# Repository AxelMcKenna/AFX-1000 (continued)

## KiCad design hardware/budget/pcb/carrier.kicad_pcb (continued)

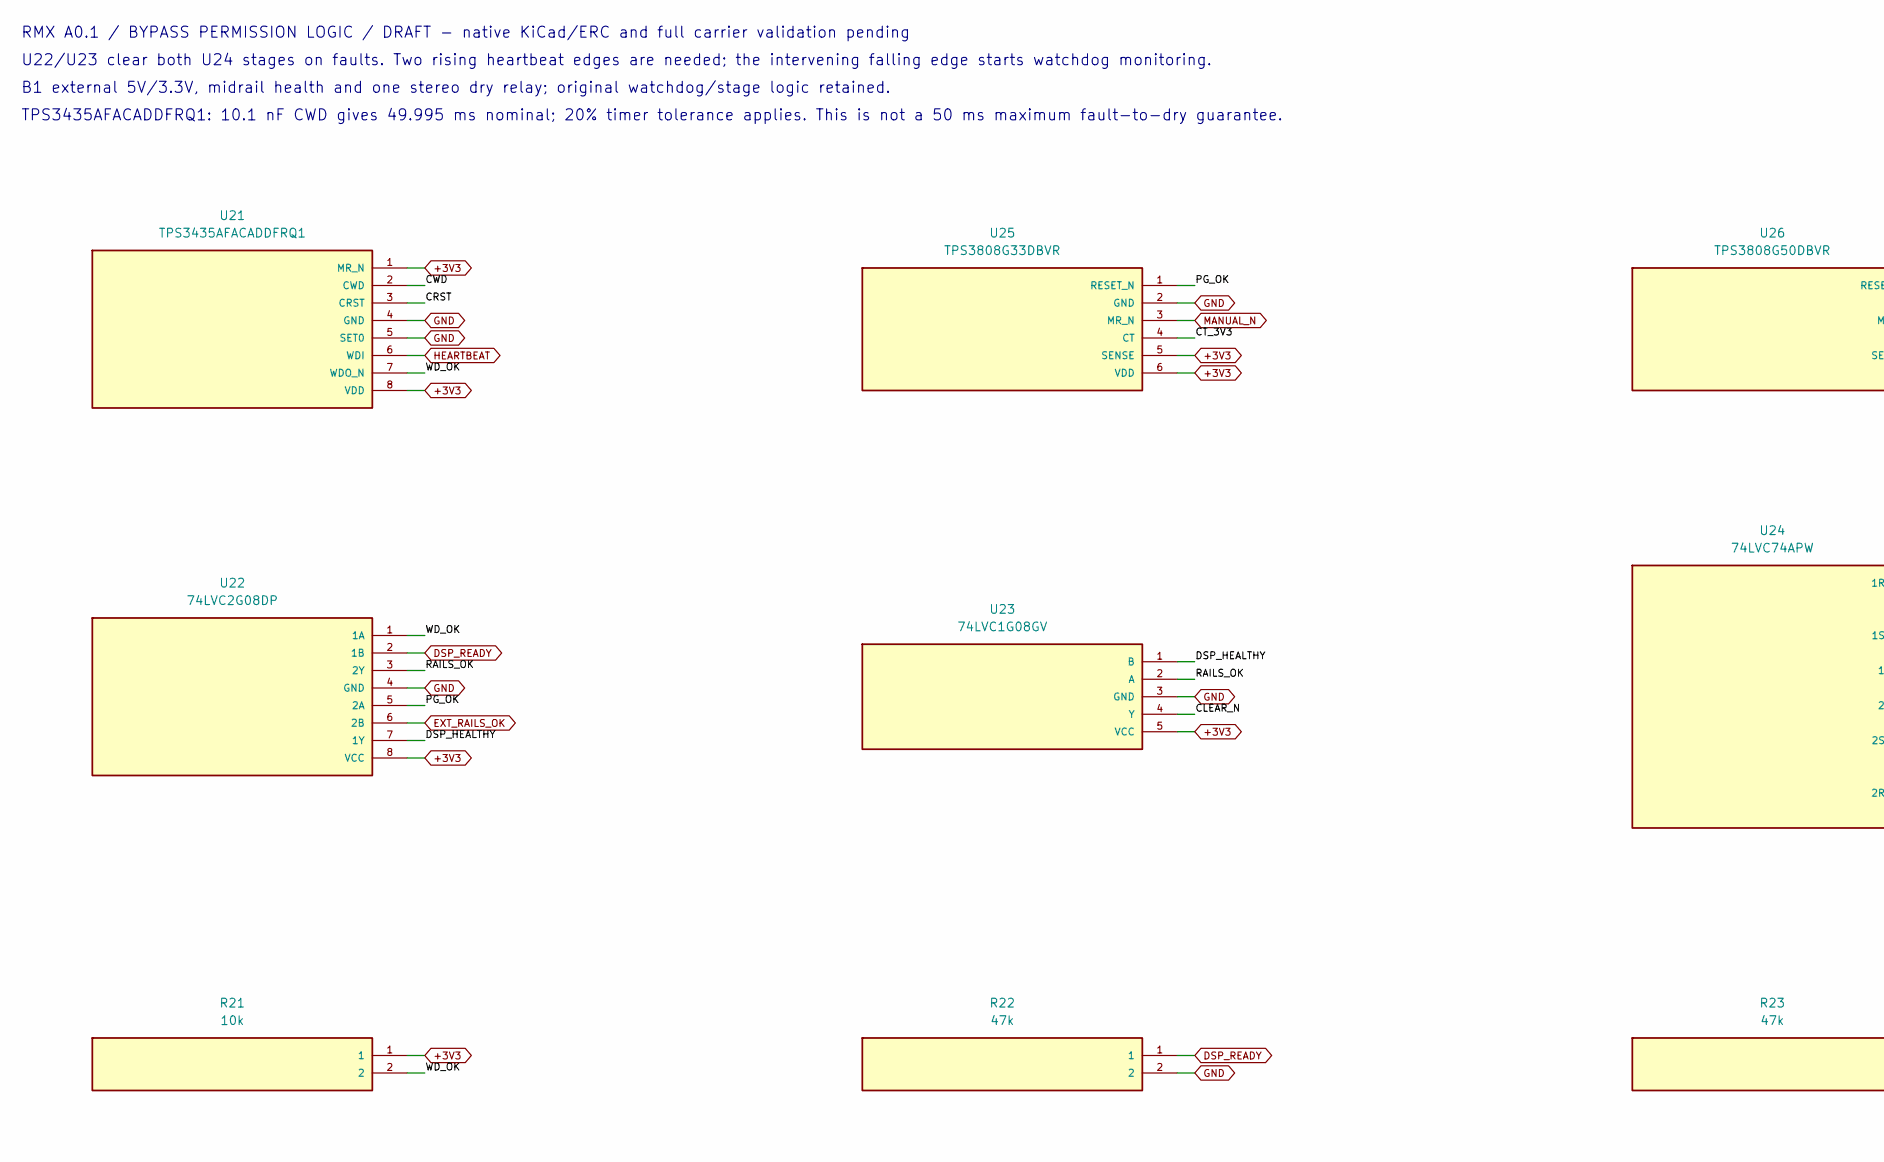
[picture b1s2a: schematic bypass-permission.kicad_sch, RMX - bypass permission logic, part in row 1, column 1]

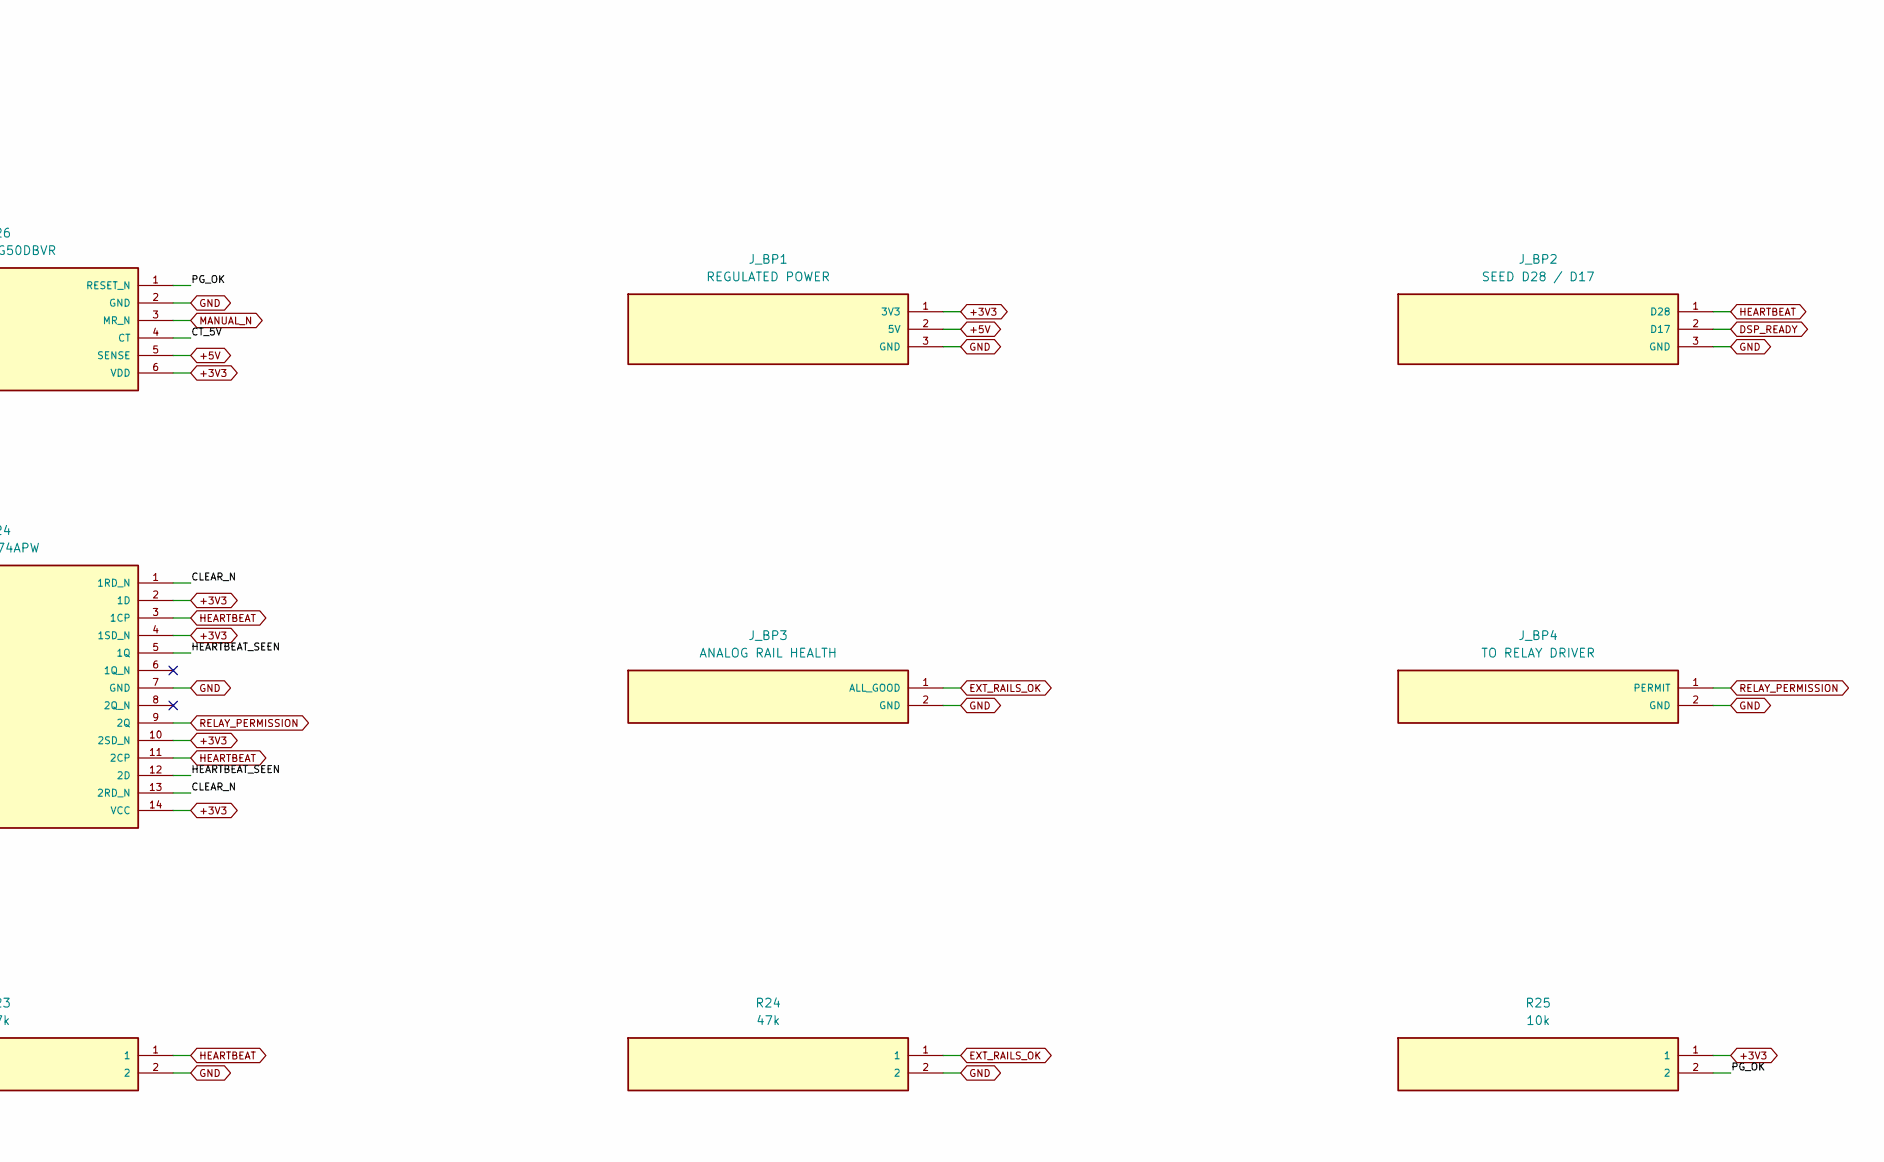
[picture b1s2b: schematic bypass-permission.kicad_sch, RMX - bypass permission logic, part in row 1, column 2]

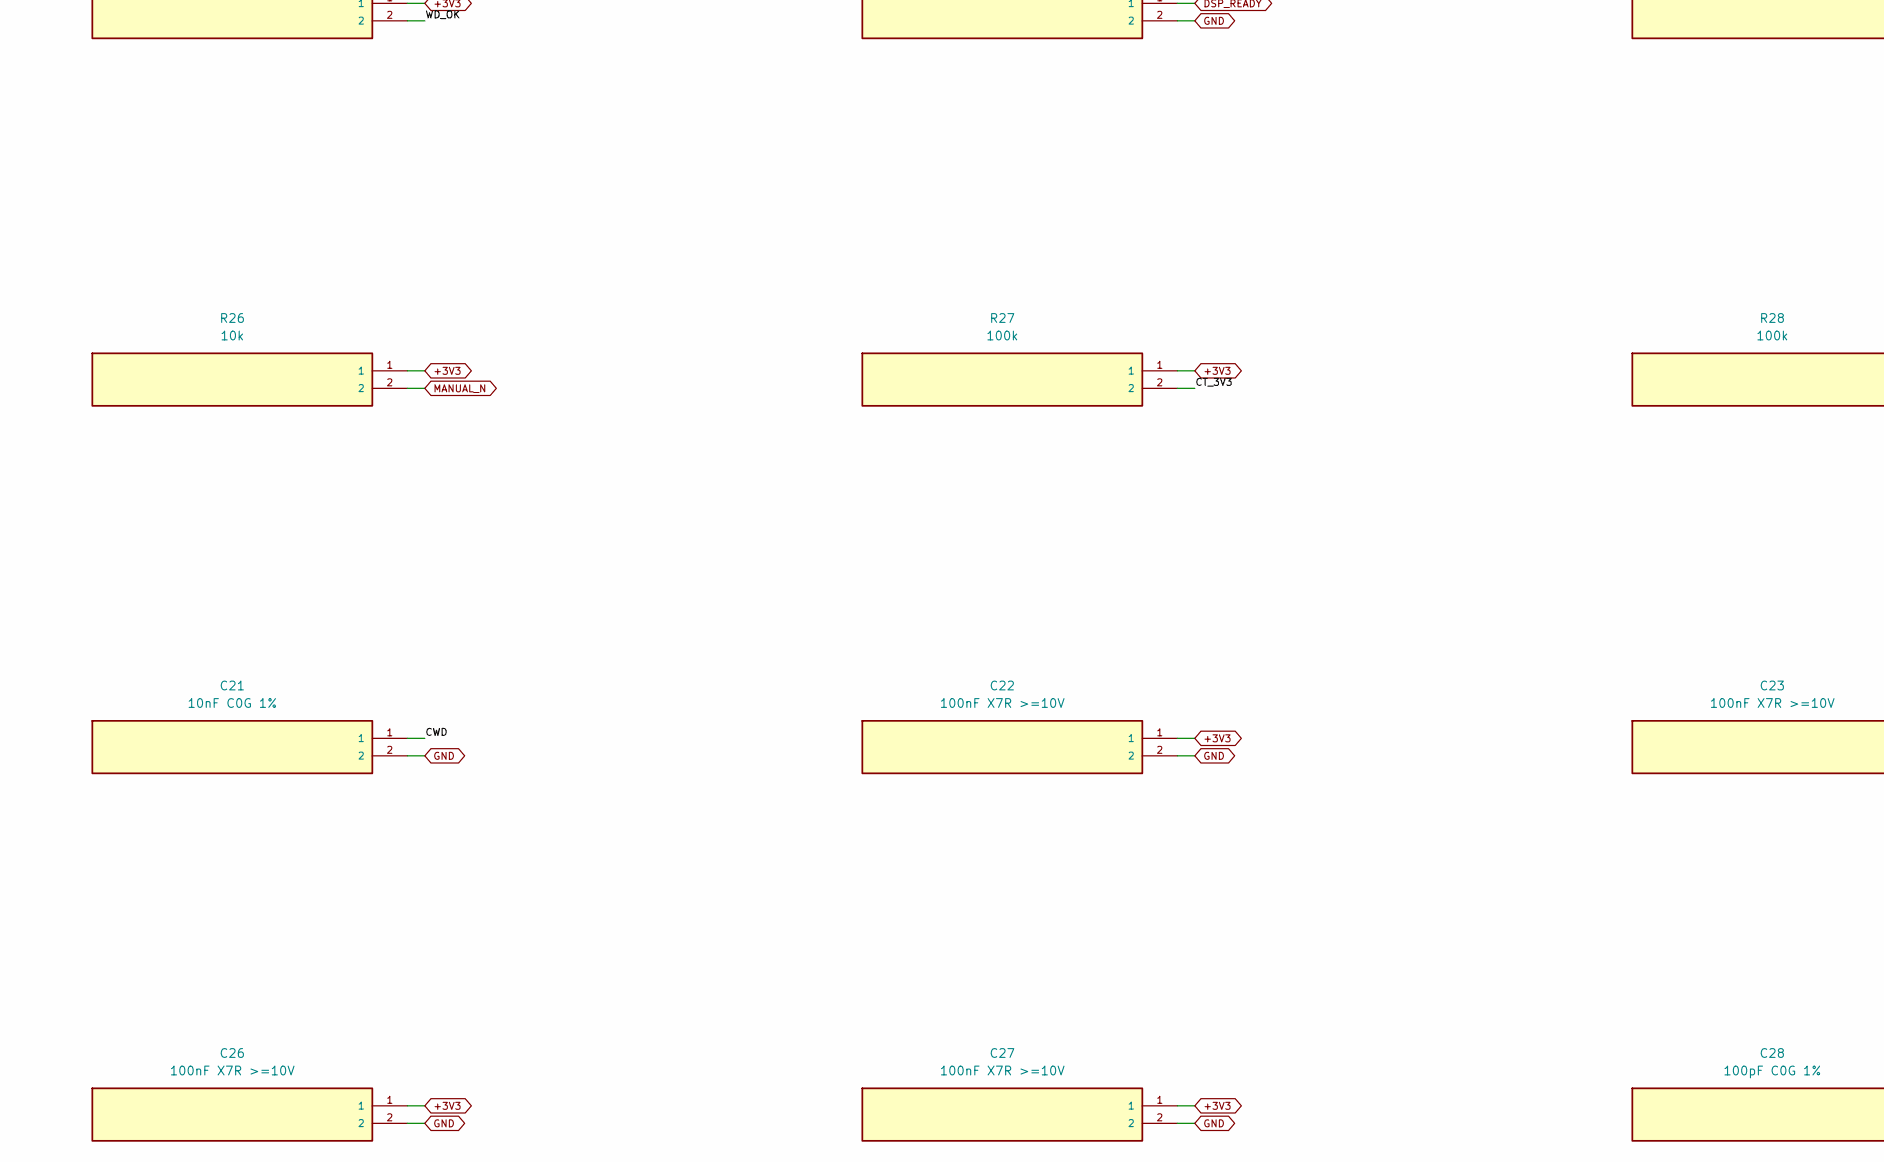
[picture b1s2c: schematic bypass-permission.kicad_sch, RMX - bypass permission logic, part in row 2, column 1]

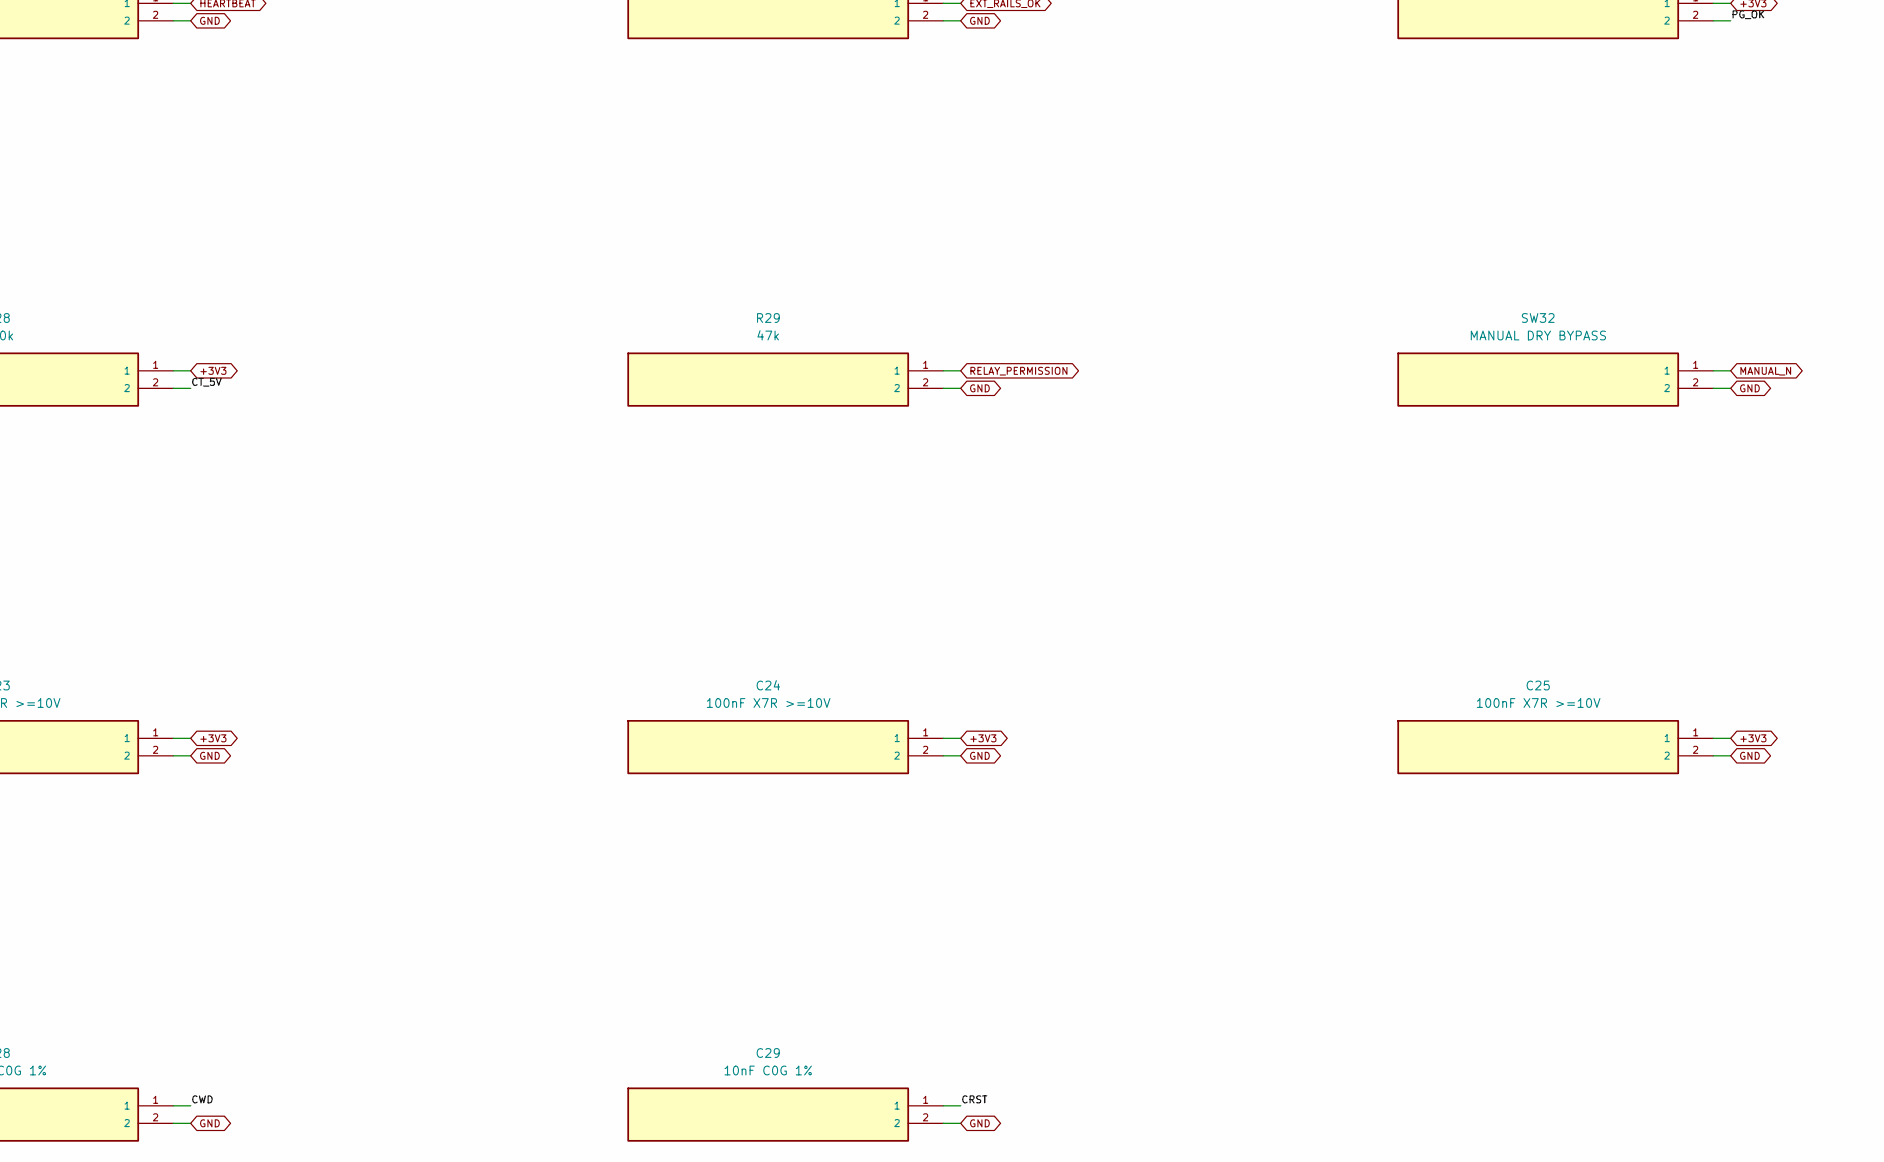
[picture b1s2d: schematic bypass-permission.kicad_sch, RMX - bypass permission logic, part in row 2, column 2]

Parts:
C21, C29: 10nF C0G 1%; C_0805_2012Metric; MPN C0805X103F5GACTU
C22, C23, C24, C25, C26, C27: 100nF X7R >=10V; C_0603_1608Metric
C28: 100pF C0G 1%; C_0603_1608Metric; MPN C0603C101F5GACTU
J_BP1: REGULATED POWER; PinHeader_1x03_P2.54mm_Vertical
J_BP2: SEED D28 / D17; PinHeader_1x03_P2.54mm_Vertical
J_BP3: ANALOG RAIL HEALTH; PinHeader_1x02_P2.54mm_Vertical
J_BP4: TO RELAY DRIVER; PinHeader_1x02_P2.54mm_Vertical
R21, R25, R26: 10k; R_0603_1608Metric; MPN RC0603FR-0710KL
R22, R23, R24, R29: 47k; R_0603_1608Metric; MPN RC0603FR-0747KL
R27, R28: 100k; R_0603_1608Metric; MPN RC0603FR-07100KL
SW32: MANUAL DRY BYPASS
U21: TPS3435AFACADDFRQ1; Texas_DDF0008A_SOT-8_1.6x2.9mm_P0.65mm; MPN TPS3435AFACADDFRQ1
U22: 74LVC2G08DP; TSSOP-8_3x3mm_P0.65mm; MPN 74LVC2G08DP
U23: 74LVC1G08GV; SOT-23-5; MPN 74LVC1G08GV
U24: 74LVC74APW; TSSOP-14_4.4x5mm_P0.65mm; MPN 74LVC74APW,118
U25: TPS3808G33DBVR; SOT-23-6; MPN TPS3808G33DBVR
U26: TPS3808G50DBVR; SOT-23-6; MPN TPS3808G50DBVR

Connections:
+3V3: C22.1, C23.1, C24.1, C25.1, C26.1, C27.1, J_BP1.1 (3V3), R21.1, R25.1, R26.1, R27.1, R28.1, U21.1 (MR_N), U21.8 (VDD), U22.8 (VCC), U23.5 (VCC), U24.2 (1D), U24.4 (1SD_N), U24.10 (2SD_N), U24.14 (VCC), U25.5 (SENSE), U25.6 (VDD), U26.6 (VDD); also elsewhere on the board
+5V: J_BP1.2 (5V), U26.5 (SENSE); also elsewhere on the board
/bypass-permission/CLEAR_N: U23.4 (Y), U24.1 (1RD_N), U24.13 (2RD_N)
/bypass-permission/CRST: C29.1, U21.3 (CRST)
/bypass-permission/CT_3V3: R27.2, U25.4 (CT)
/bypass-permission/CT_5V: R28.2, U26.4 (CT)
/bypass-permission/CWD: C21.1, C28.1, U21.2 (CWD)
/bypass-permission/DSP_HEALTHY: U22.7 (1Y), U23.1 (B)
/bypass-permission/HEARTBEAT_SEEN: U24.5 (1Q), U24.12 (2D)
/bypass-permission/PG_OK: R25.2, U22.5 (2A), U25.1 (RESET_N), U26.1 (RESET_N)
/bypass-permission/RAILS_OK: U22.3 (2Y), U23.2 (A)
/bypass-permission/WD_OK: R21.2, U21.7 (WDO_N), U22.1 (1A)
DSP_READY: J_BP2.2 (D17), R22.1, U22.2 (1B)
EXT_RAILS_OK: J_BP3.1 (ALL_GOOD), R24.1, U22.6 (2B); also elsewhere on the board
GND: C21.2, C22.2, C23.2, C24.2, C25.2, C26.2, C27.2, C28.2, C29.2, J_BP1.3 (GND), J_BP2.3 (GND), J_BP3.2 (GND), J_BP4.2 (GND), R22.2, R23.2, R24.2, R29.2, SW32.2, U21.4 (GND), U21.5 (SET0), U22.4 (GND), U23.3 (GND), U24.7 (GND), U25.2 (GND), U26.2 (GND); also elsewhere on the board
HEARTBEAT: J_BP2.1 (D28), R23.1, U21.6 (WDI), U24.3 (1CP), U24.11 (2CP)
MANUAL_N: R26.2, SW32.1, U25.3 (MR_N), U26.3 (MR_N); also elsewhere on the board
RELAY_PERMISSION: J_BP4.1 (PERMIT), R29.1, U24.9 (2Q); also elsewhere on the board

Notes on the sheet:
RMX A0.1 / BYPASS PERMISSION LOGIC / DRAFT - native KiCad/ERC and full carrier validation pending
U22/U23 clear both U24 stages on faults. Two rising heartbeat edges are needed; the intervening falling edge starts watchdog monitoring.
B1 external 5V/3.3V, midrail health and one stereo dry relay; original watchdog/stage logic retained.
TPS3435AFACADDFRQ1: 10.1 nF CWD gives 49.995 ms nominal; 20% timer tolerance applies. This is not a 50 ms maximum fault-to-dry guarantee.

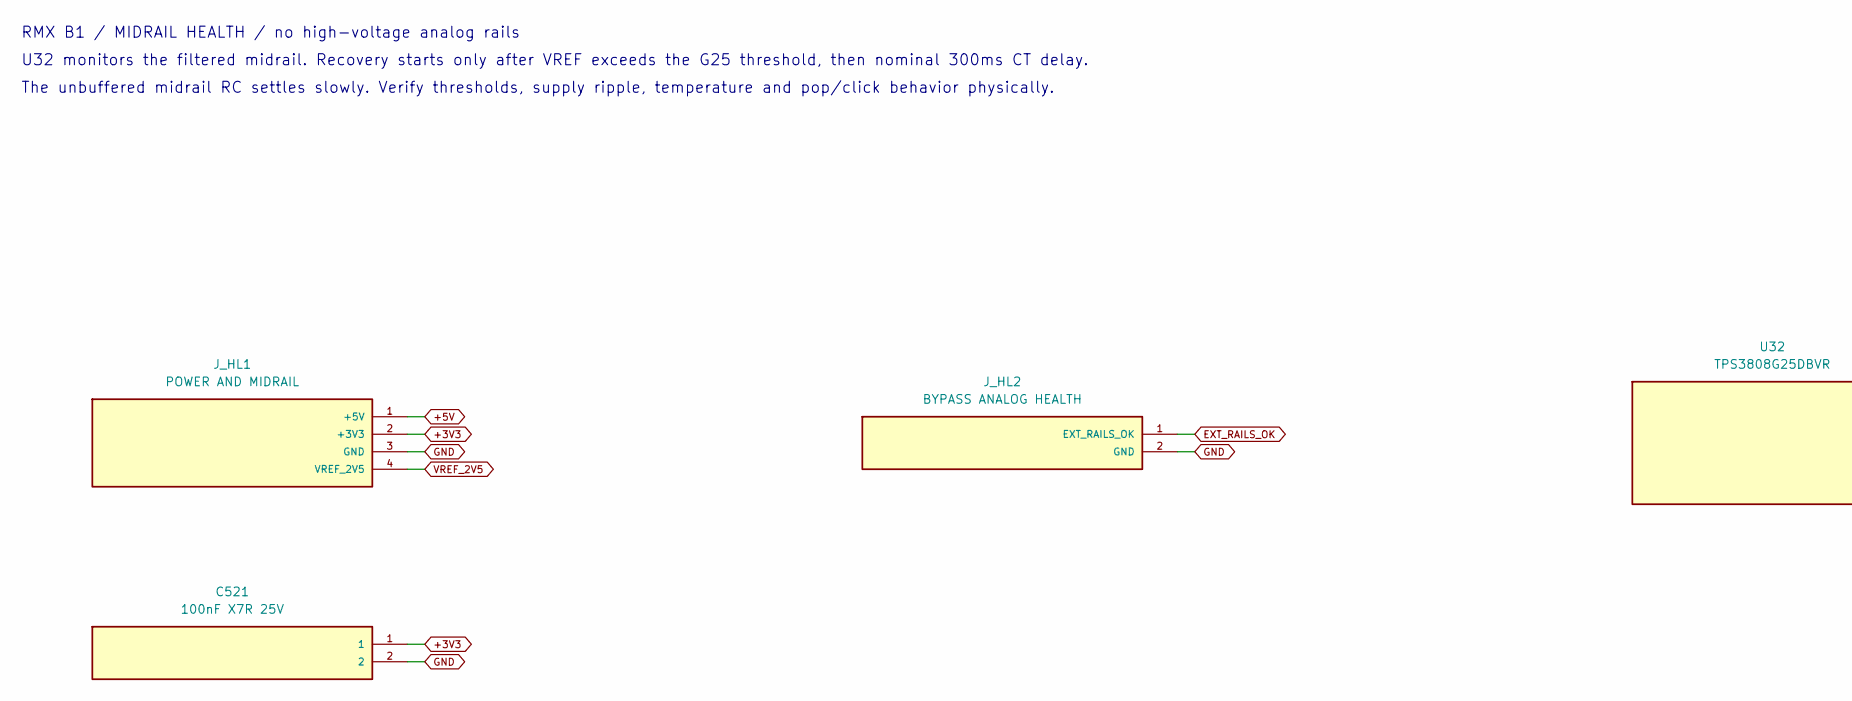
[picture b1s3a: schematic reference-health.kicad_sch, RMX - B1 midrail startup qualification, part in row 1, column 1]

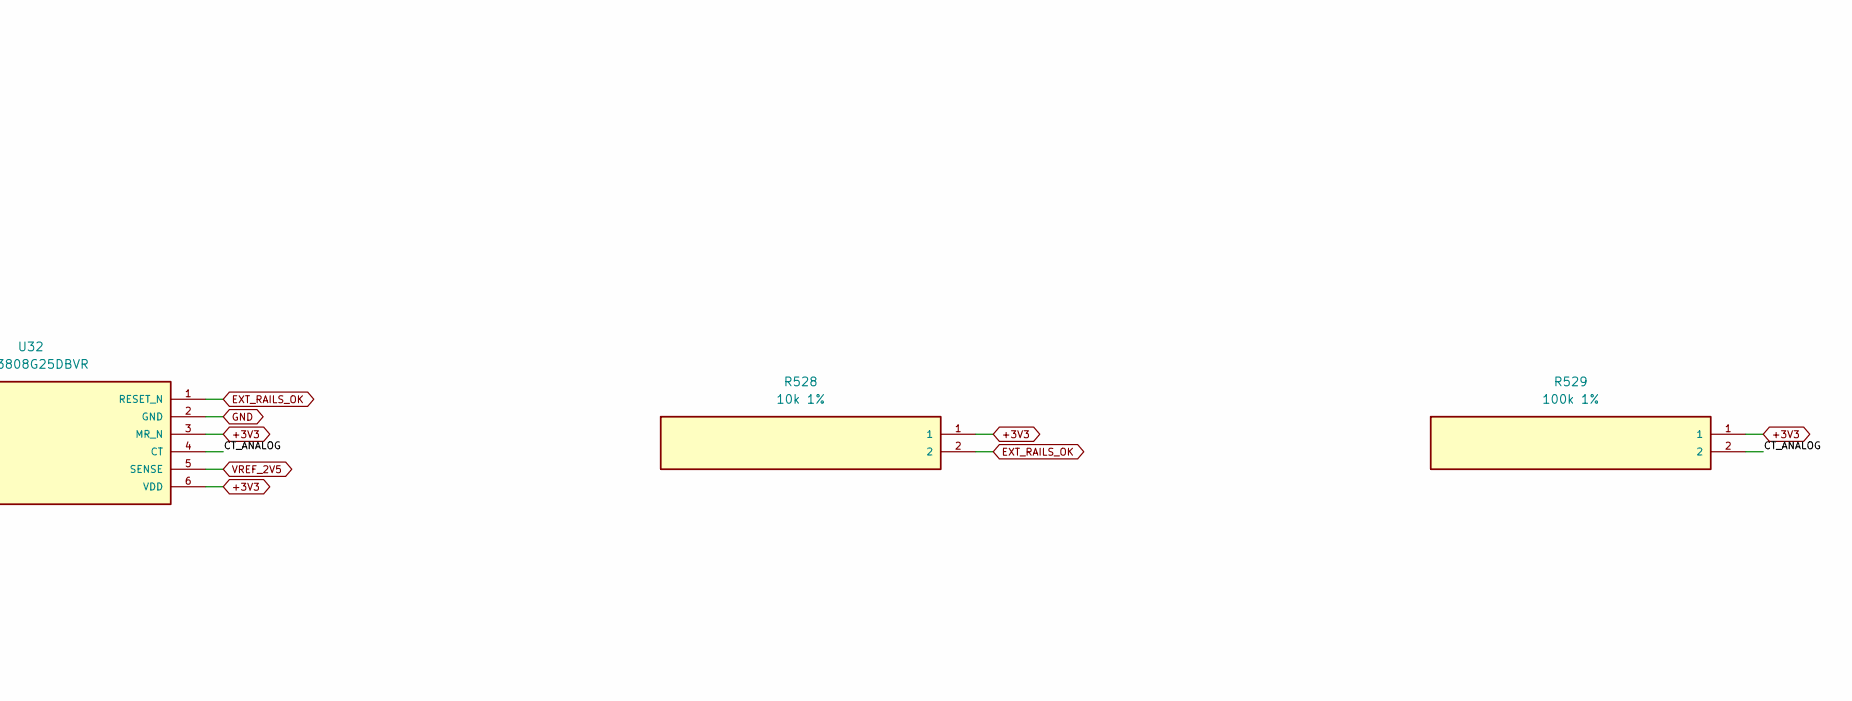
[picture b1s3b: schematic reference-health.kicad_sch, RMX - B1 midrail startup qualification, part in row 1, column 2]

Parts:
C521: 100nF X7R 25V; C_0805_2012Metric
J_HL1: POWER AND MIDRAIL; PinHeader_1x04_P2.54mm_Vertical
J_HL2: BYPASS ANALOG HEALTH; PinHeader_1x02_P2.54mm_Vertical
R528: 10k 1%; R_0603_1608Metric; MPN RC0603FR-0710KL
R529: 100k 1%; R_0603_1608Metric; MPN RC0603FR-07100KL
U32: TPS3808G25DBVR; SOT-23-6; MPN TPS3808G25DBVR

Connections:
+3V3: C521.1, J_HL1.2 (+3V3), R528.1, R529.1, U32.3 (MR_N), U32.6 (VDD); also elsewhere on the board
+5V: J_HL1.1 (+5V); also elsewhere on the board
/reference-health/CT_ANALOG: R529.2, U32.4 (CT)
EXT_RAILS_OK: J_HL2.1 (EXT_RAILS_OK), R528.2, U32.1 (RESET_N); also elsewhere on the board
GND: C521.2, J_HL1.3 (GND), J_HL2.2 (GND), U32.2 (GND); also elsewhere on the board
VREF_2V5: J_HL1.4 (VREF_2V5), U32.5 (SENSE); also elsewhere on the board

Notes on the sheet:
RMX B1 / MIDRAIL HEALTH / no high-voltage analog rails
U32 monitors the filtered midrail. Recovery starts only after VREF exceeds the G25 threshold, then nominal 300ms CT delay.
The unbuffered midrail RC settles slowly. Verify thresholds, supply ripple, temperature and pop/click behavior physically.

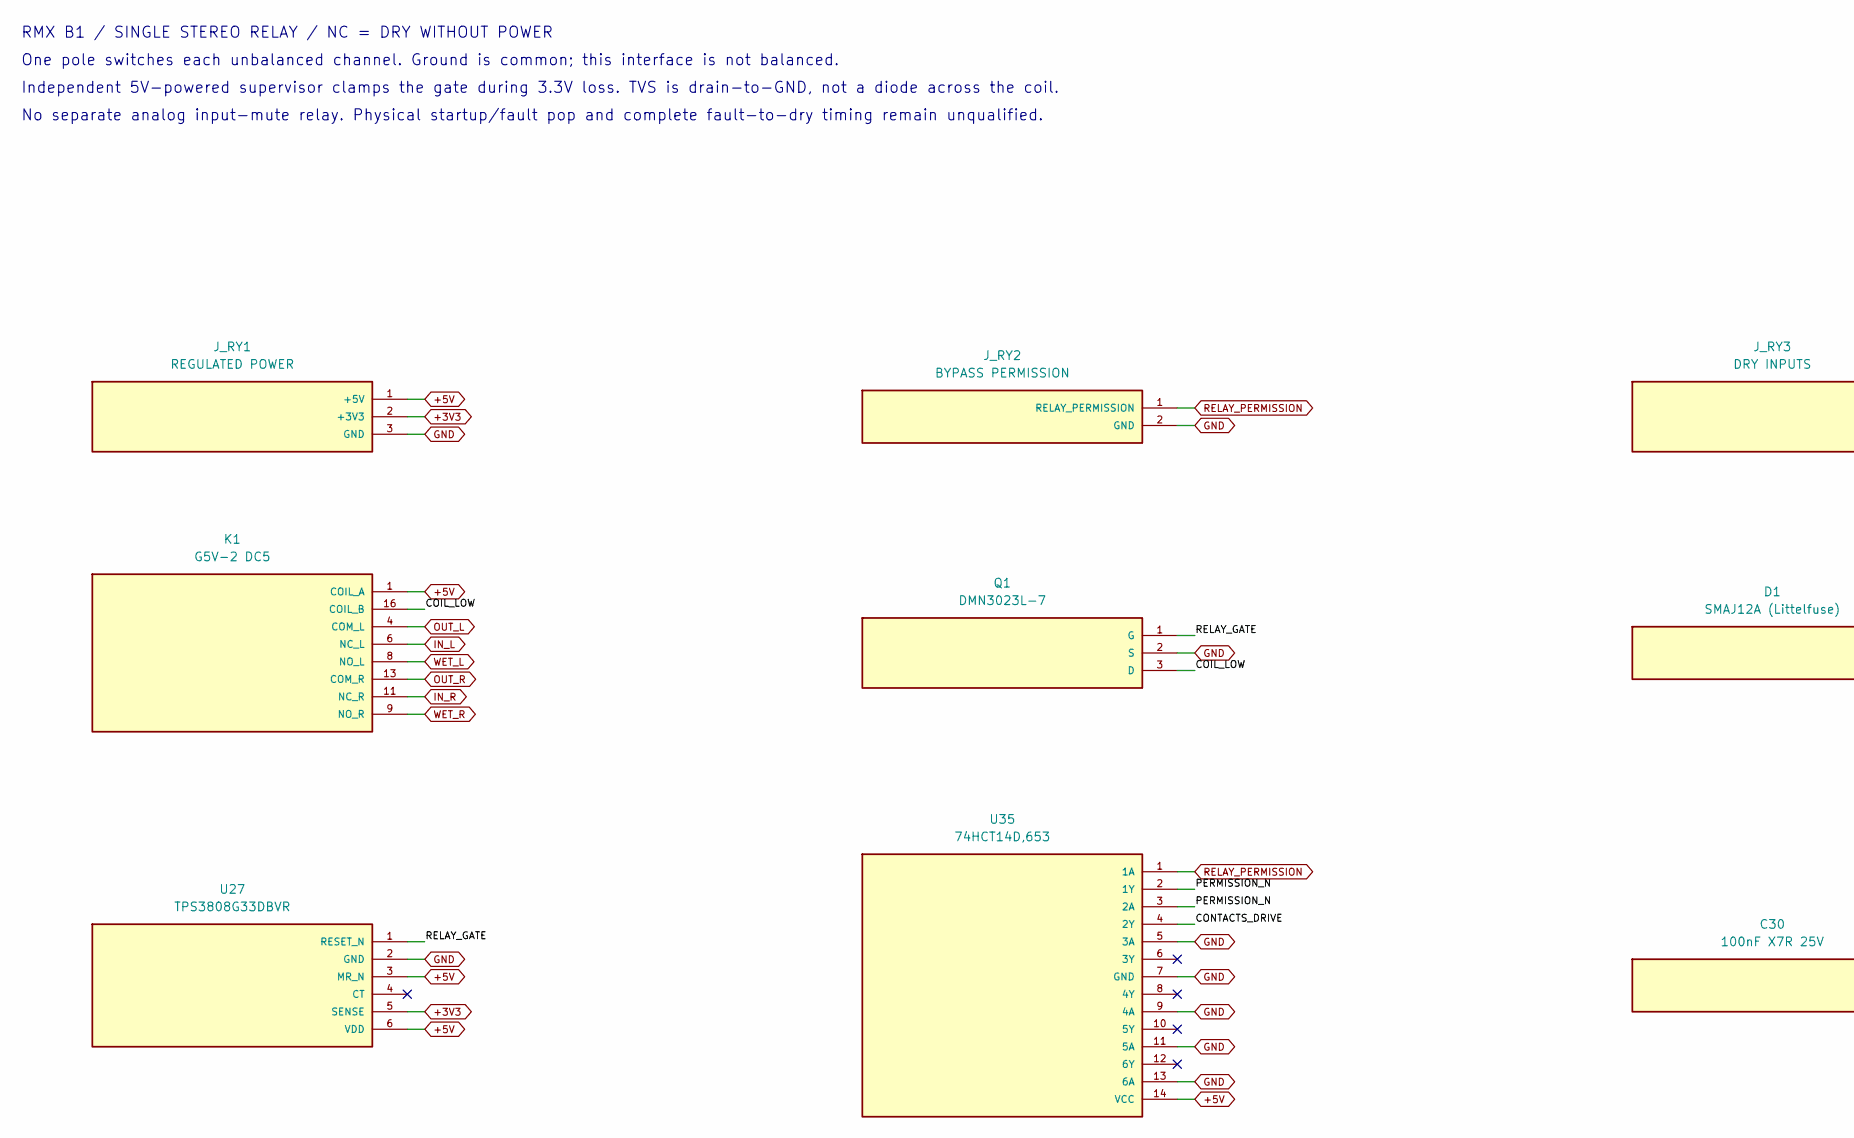
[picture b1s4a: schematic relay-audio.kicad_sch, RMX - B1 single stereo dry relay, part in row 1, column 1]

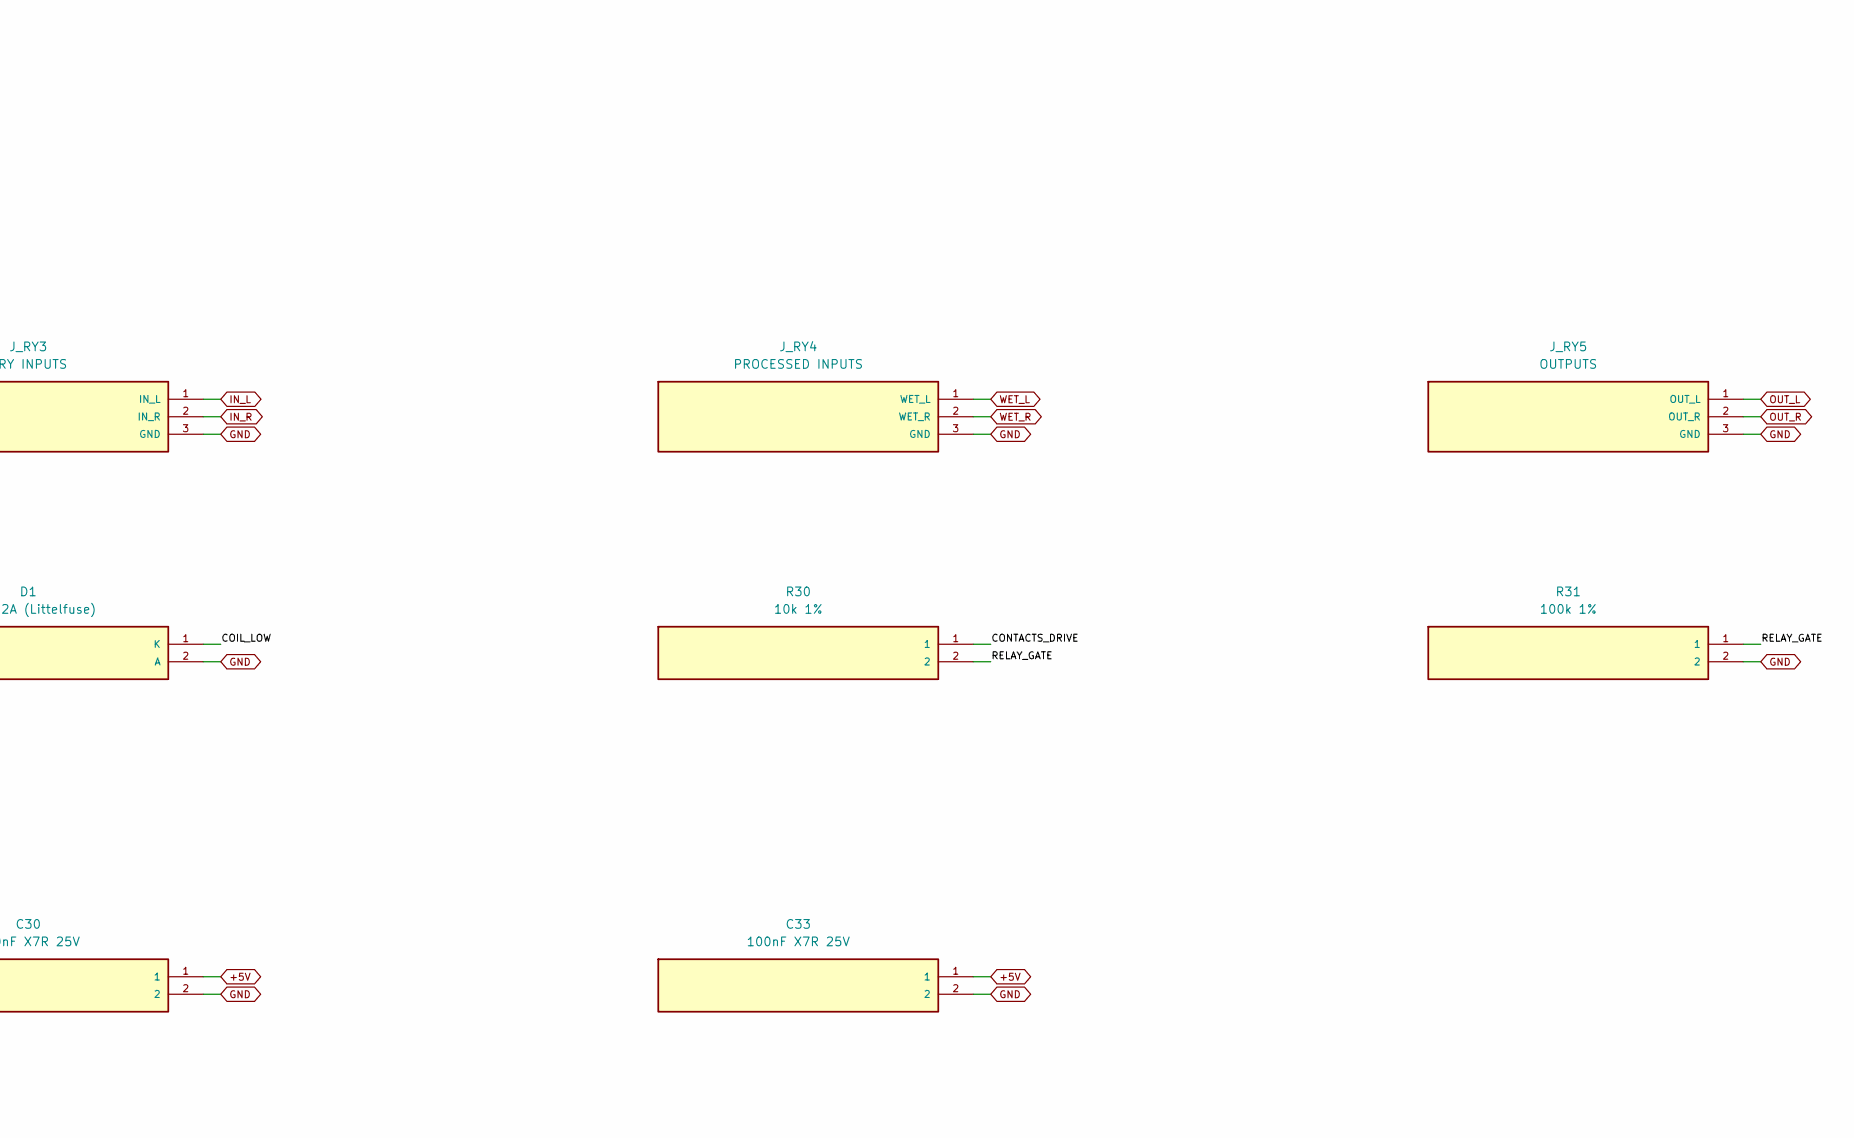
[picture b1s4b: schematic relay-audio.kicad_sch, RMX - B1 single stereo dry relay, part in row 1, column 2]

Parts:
C30, C33: 100nF X7R 25V; C_0805_2012Metric
D1: SMAJ12A (Littelfuse); D_SMA; MPN SMAJ12A
J_RY1: REGULATED POWER; PinHeader_1x03_P2.54mm_Vertical
J_RY2: BYPASS PERMISSION; PinHeader_1x02_P2.54mm_Vertical
J_RY3: DRY INPUTS; PinHeader_1x03_P2.54mm_Vertical
J_RY4: PROCESSED INPUTS; PinHeader_1x03_P2.54mm_Vertical
J_RY5: OUTPUTS; PinHeader_1x03_P2.54mm_Vertical
K1: G5V-2 DC5; Relay_DPDT_Omron_G5V-2; MPN G5V-2 DC5
Q1: DMN3023L-7; SOT-23; MPN DMN3023L-7
R30: 10k 1%; R_0603_1608Metric; MPN RC0603FR-0710KL
R31: 100k 1%; R_0603_1608Metric; MPN RC0603FR-07100KL
U27: TPS3808G33DBVR; SOT-23-6; MPN TPS3808G33DBVR
U35: 74HCT14D,653; SOIC-14_3.9x8.7mm_P1.27mm; MPN 74HCT14D,653

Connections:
+3V3: J_RY1.2 (+3V3), U27.5 (SENSE); also elsewhere on the board
+5V: C30.1, C33.1, J_RY1.1 (+5V), K1.1 (COIL_A), U27.3 (MR_N), U27.6 (VDD), U35.14 (VCC); also elsewhere on the board
/relay-audio/COIL_LOW: D1.1 (K), K1.16 (COIL_B), Q1.3 (D)
/relay-audio/CONTACTS_DRIVE: R30.1, U35.4 (2Y)
/relay-audio/PERMISSION_N: U35.2 (1Y), U35.3 (2A)
/relay-audio/RELAY_GATE: Q1.1 (G), R30.2, R31.1, U27.1 (RESET_N)
GND: C30.2, C33.2, D1.2 (A), J_RY1.3 (GND), J_RY2.2 (GND), J_RY3.3 (GND), J_RY4.3 (GND), J_RY5.3 (GND), Q1.2 (S), R31.2, U27.2 (GND), U35.5 (3A), U35.7 (GND), U35.9 (4A), U35.11 (5A), U35.13 (6A); also elsewhere on the board
IN_L: J_RY3.1 (IN_L), K1.6 (NC_L); also elsewhere on the board
IN_R: J_RY3.2 (IN_R), K1.11 (NC_R); also elsewhere on the board
OUT_L: J_RY5.1 (OUT_L), K1.4 (COM_L); also elsewhere on the board
OUT_R: J_RY5.2 (OUT_R), K1.13 (COM_R); also elsewhere on the board
RELAY_PERMISSION: J_RY2.1 (RELAY_PERMISSION), U35.1 (1A); also elsewhere on the board
WET_L: J_RY4.1 (WET_L), K1.8 (NO_L); also elsewhere on the board
WET_R: J_RY4.2 (WET_R), K1.9 (NO_R); also elsewhere on the board

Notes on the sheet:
RMX B1 / SINGLE STEREO RELAY / NC = DRY WITHOUT POWER
One pole switches each unbalanced channel. Ground is common; this interface is not balanced.
Independent 5V-powered supervisor clamps the gate during 3.3V loss. TVS is drain-to-GND, not a diode across the coil.
No separate analog input-mute relay. Physical startup/fault pop and complete fault-to-dry timing remain unqualified.

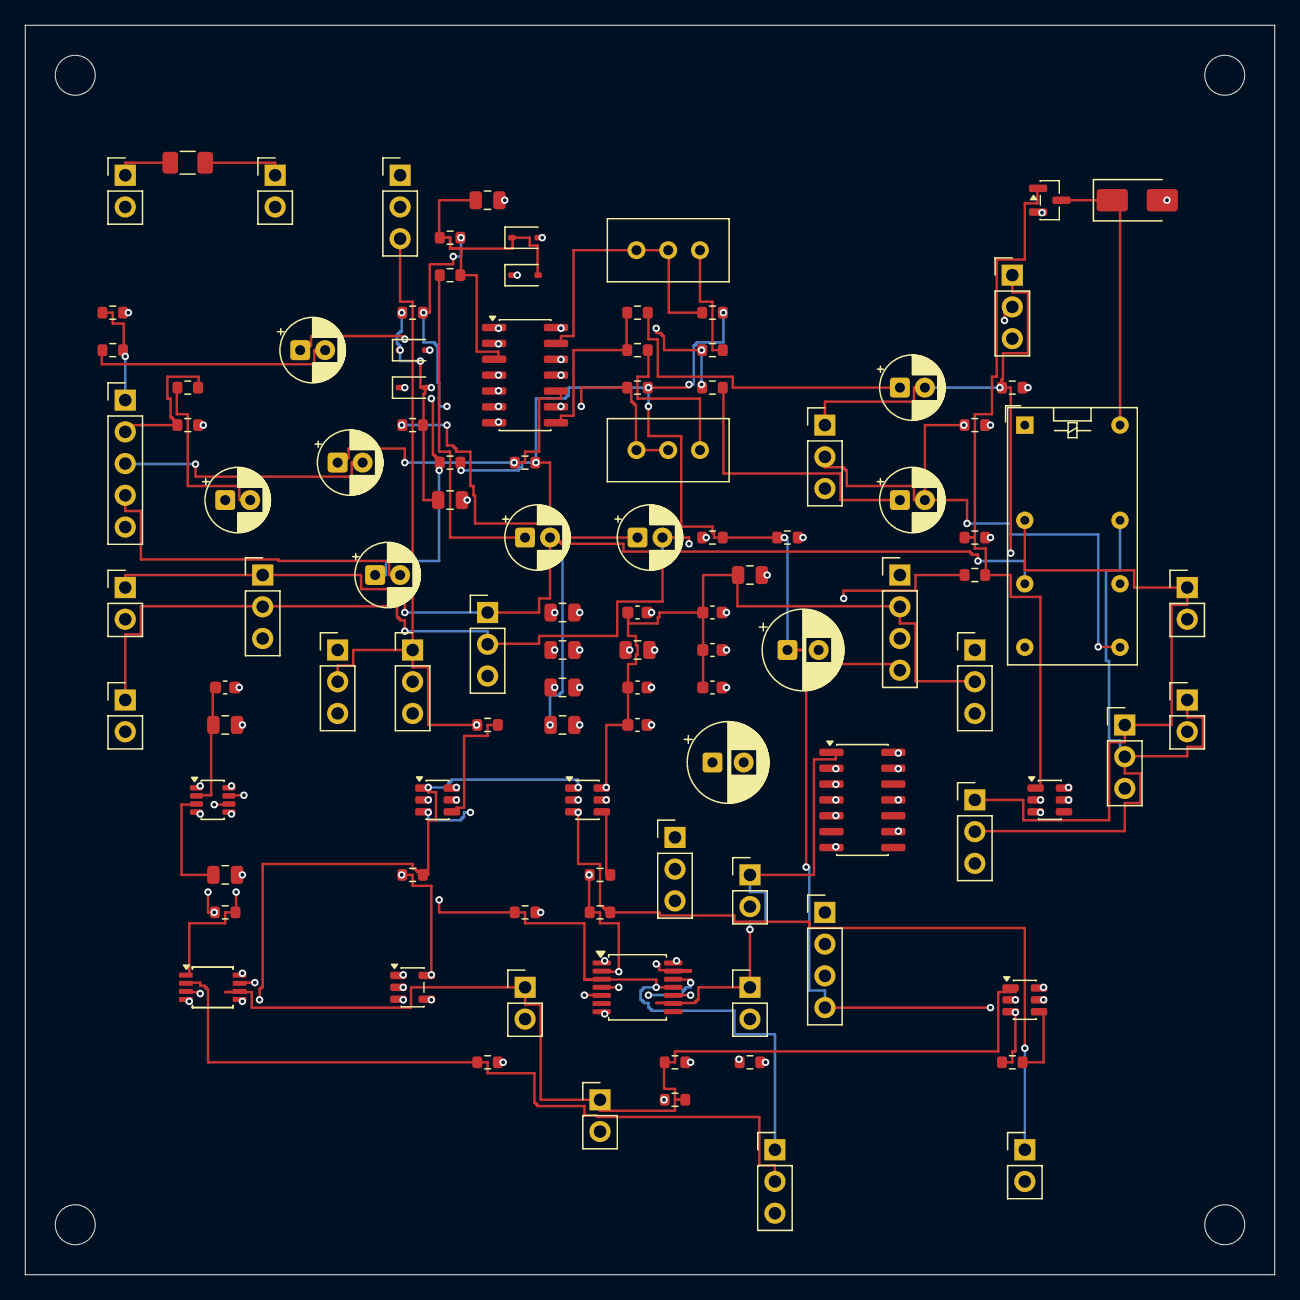
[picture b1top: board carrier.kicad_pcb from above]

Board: 4 copper layers, 100.0 x 100.0 mm, 110 parts (0 on the bottom side), 54 nets.

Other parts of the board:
H1, H2, H3, H4: MountingHole_3.2mm_M3
